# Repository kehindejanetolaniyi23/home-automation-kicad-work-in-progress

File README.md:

# Home Automation Relay and Power Monitoring PCB — Work in Progress

This repository contains my ongoing KiCad PCB design for a home automation relay and power monitoring board.

The project is designed as a multi-channel control and monitoring board for home automation applications. It combines relay switching, power monitoring, sensing interfaces, optocoupler isolation, and onboard power regulation into one PCB design.

This project is still in progress, and I am continuing to improve the routing, board outline, component spacing, and design rule compliance.

## Project Overview

The goal of this project is to design a PCB that can support home automation control and electrical monitoring functions. The board includes relay outputs for switching external loads, sensing sections for voltage/current monitoring, and interface connections for a controller module.

The design is being developed in KiCad and currently includes both schematic and PCB layout files.

## Main Features

* Multi-channel relay switching section
* Optocoupler isolation stage
* Voltage sensing section
* Current sensing transformer section
* Onboard power regulation section
* Screw terminal input/output connectors
* Status indicator LEDs
* Controller/header interface
* Two-layer PCB layout
* KiCad schematic and PCB layout files

## Tools Used

* KiCad
* KiCad Schematic Editor
* KiCad PCB Editor
* KiCad Design Rules Checker

## Repository Files

This repository includes:

* `homeautomation2.kicad_pro` — KiCad project file
* `homeautomation2.kicad_sch` — schematic design file
* `homeautomation2.kicad_pcb` — PCB layout file
* Screenshot images showing the schematic, PCB layout, and current DRC result

## Current Status

Status: **Work in Progress**

The schematic and PCB layout have been created and opened successfully in KiCad. The design already contains the major functional blocks for relay control, sensing, power regulation, and external wiring connections.

The PCB layout is still being improved. Current work includes:

* Completing remaining unrouted connections
* Fixing board outline issues
* Improving component spacing
* Cleaning up silkscreen placement
* Resolving DRC errors and warnings
* Preparing the board for a cleaner final layout
* Generating Gerber files only after the design passes final checks

## Design Notes

The board is intended to combine control and monitoring functions in a compact home automation PCB. The relay section is used for switching loads, while the sensing section supports electrical monitoring. Optocouplers are included to improve isolation between the control and switching sections.

The current PCB layout is functional as a design draft, but it is not yet marked as manufacturing-ready. I am still refining the routing and resolving design rule issues before producing final Gerber fabrication files.

## Next Improvements

The next development steps are:

1. Complete all remaining PCB routing.
2. Fix the Edge.Cuts board outline.
3. Resolve all Design Rule Check errors.
4. Improve relay, terminal block, and sensing section spacing.
5. Clean up text labels and silkscreen placement.
6. Re-run schematic-to-PCB checks.
7. Re-run DRC until the project has zero errors.
8. Export Gerber and drill files after the design is fully cleaned.

## Project Purpose

This project demonstrates my ongoing KiCad PCB design workflow, including schematic capture, PCB layout development, routing, DRC checking, and iterative board improvement.

The design is still under development and will be updated as improvements are made.

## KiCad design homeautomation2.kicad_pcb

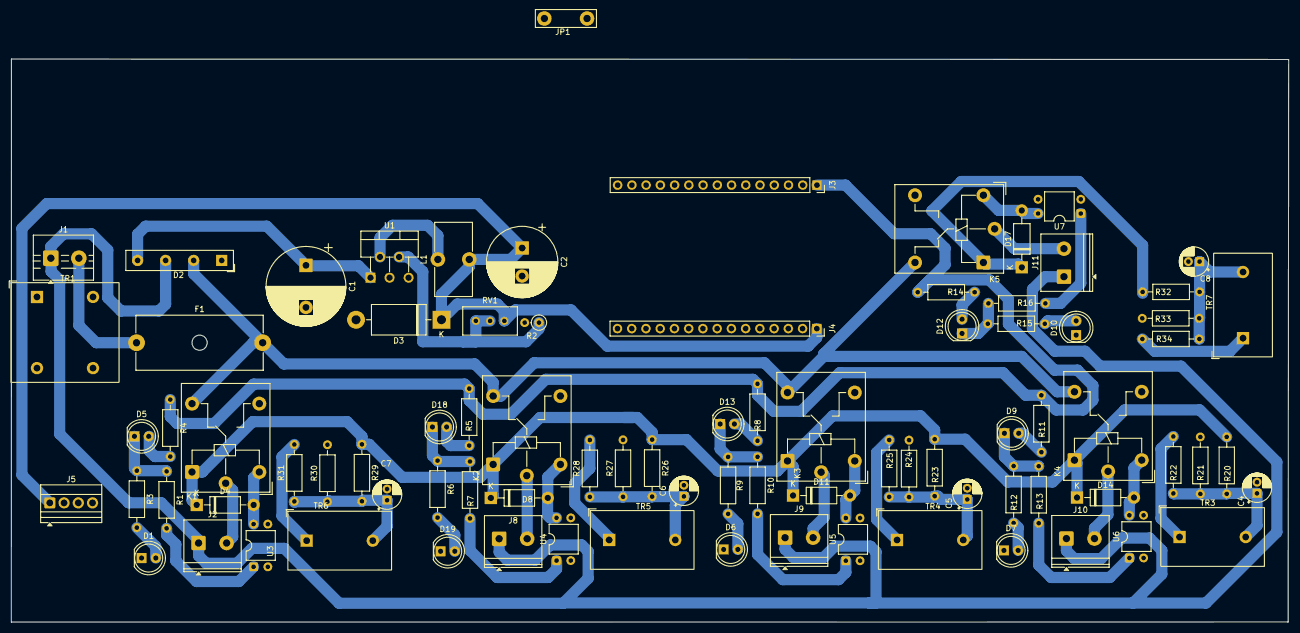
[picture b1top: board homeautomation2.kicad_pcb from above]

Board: 2 copper layers, 227.9 x 100.4 mm, 85 parts (0 on the bottom side), 50 nets.

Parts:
C1: C_Polarized; CP_Radial_D14.0mm_P7.50mm
C2: C_Polarized; CP_Radial_D12.5mm_P5.00mm
C4, C5, C6, C7, C8: C_Small_US; CP_Radial_D5.0mm_P2.00mm
D1, D6, D7, D10, D19: LED; LED_D5.0mm
D2: B500C2300-1500A; Diode_Bridge_19.0x3.5x10.0mm_P5.0mm
D3: 1N5822; D_DO-201AD_P15.24mm_Horizontal
D4, D8, D11, D14, D17: 1N4007; D_DO-41_SOD81_P10.16mm_Horizontal
D5, D9, D12, D13, D18: LED; LED_D5.0mm_Clear
F1: Fuse; Fuseholder_Cylinder-5x20mm_Schurter_0031_8201_Horizontal_Op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
J1: Screw_Terminal_01x02; TerminalBlock_MaiXu_MX126-5.0-02P_1x02_P5.00mm
J2, J8, J9, J10, J11: Screw_Terminal_01x02; TerminalBlock_Phoenix_PT-1,5-2-5.0-H_1x02_P5.00mm_Horizontal
J3, J4: Conn_01x15_Socket; PinSocket_1x15_P2.54mm_Vertical
J5: Conn_01x04_Socket; TerminalBlock_Xinya_XY308-2.54-4P_1x04_P2.54mm_Horizontal
JP1: Jumper_2_Bridged; TestPoint_Bridge_Pitch7.62mm_Drill1.3mm
K1, K2, K3, K4, K5: JQC-3FF-005-1Z; Relay_SPDT_Hongfa_JQC-3FF_0XX-1Z
L1: L_Ferrite_Small; L_Toroid_Vertical_L13.0mm_W6.5mm_P5.60mm
R1, R3, R4, R5, R6, R7, R8, R9, R10, R11, R12, R13, R14, R15, R16, R20, R21, R22, R23, R24, R25, R26, R27, R28, R29, R30, R31, R32, R33, R34: R_Small; R_Axial_DIN0207_L6.3mm_D2.5mm_P10.16mm_Horizontal
R2: R_Small; R_Axial_DIN0207_L6.3mm_D2.5mm_P2.54mm_Vertical
RV1: R_Potentiometer_Small; Potentiometer_Bourns_3296W_Vertical
TR1: ZMPT101K; Transformer_Zeming_ZMPT101K
TR3, TR4, TR5, TR6, TR7: ZMCT103C; Transformer_Zeming_ZMCT103C
U1: LM2596T-5; TO-220-5_P3.4x3.7mm_StaggerOdd_Lead3.8mm_Vertical
U3, U4, U5, U6, U7: PC817; DIP-4_W7.62mm

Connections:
+3.3V: J3.1, R4.1, R5.1, R8.1, R11.1, R14.1
+5V: C2.1, D3.1 (K), D4.1 (K), D8.1 (K), D11.1 (K), D14.1 (K), D17.1 (K), J4.1, J5.1, K1.A1, K2.A1, K3.A1, K4.A1, K5.A1, L1.2, R20.1, R23.1, R26.1, R29.1, R32.1, RV1.1
Earth: C1.2, C2.2, C4.2, C5.2, C6.2, C7.2, C8.2, D1.1 (K), D2.1 (-), D3.2 (A), D6.1 (K), D7.1 (K), D10.1 (K), D19.1 (K), J3.2, J4.2, J5.3, J5.4, R2.2, R21.2, R24.2, R27.2, R30.2, R33.2, U1.3 (GND), U1.5 (~ON/OFF), U3.2, U3.3, U4.2, U4.3, U5.2, U5.3, U6.2, U6.3, U7.2, U7.3
unnamed: C4.1, R20.2, R21.1, R22.1, TR3.2
unnamed: C5.1, R23.2, R24.1, R25.1, TR4.2
unnamed: C6.1, R26.2, R27.1, R28.1, TR5.2
unnamed: C7.1, R29.2, R30.1, R31.1, TR6.2
unnamed: C8.1, R32.2, R33.1, R34.1, TR7.2
unnamed: D1.2 (A), R3.2
unnamed: C1.1, D2.4 (+), U1.1 (VIN)
unnamed: D4.2 (A), K1.A2, U3.4
unnamed: D5.2 (A), R4.2
unnamed: D6.2 (A), R9.2
unnamed: D7.2 (A), R12.2
unnamed: D8.2 (A), K2.A2, U4.4
unnamed: D9.2 (A), R11.2
unnamed: D10.2 (A), R15.2
unnamed: D11.2 (A), K3.A2, U5.4
unnamed: D12.2 (A), R14.2
unnamed: D13.2 (A), R8.2
unnamed: D14.2 (A), K4.A2, U6.4
unnamed: D17.2 (A), K5.A2, U7.4
unnamed: D18.2 (A), R5.2
unnamed: D19.2 (A), R6.2
unnamed: F1.1, J1.2
unnamed: J2.2, K1.11
unnamed: J8.2, K2.11
unnamed: J9.2, K3.11
unnamed: J10.2, K4.11
unnamed: J11.2, K5.11
unnamed: R1.2, U3.1
unnamed: R7.2, U4.1
unnamed: R10.2, U5.1
unnamed: R13.2, U6.1
unnamed: R16.2, U7.1
unnamed: R2.1, RV1.2, RV1.3, U1.4 (FB)
unnamed: L1.1, U1.2 (OUT)
Vout: J4.9, J5.2
cur1: J4.10, R34.2, TR7.1
cur2: J4.11, R22.2, TR3.1
cur3: J4.12, R25.2, TR4.1
cur4: J4.13, R28.2, TR5.1
cur5: J4.14, R31.2, TR6.1
live: D2.2, F1.2, K1.12, K2.12, K3.12, K4.12, K5.12
neutral: D2.3, J1.1, J2.1, J8.1, J9.1, J10.1, J11.1
relay1: D12.1 (K), J4.3, R15.1, R16.1
relay2: D9.1 (K), J4.5, R12.1, R13.1
relay3: D13.1 (K), J4.6, R9.1, R10.1
relay4: D18.1 (K), J4.7, R6.1, R7.1
relay5: D5.1 (K), J4.8, R1.1, R3.1

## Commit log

2026-06-25 Add home automation KiCad work-in-progress files
2026-06-25 Revise README for home automation PCB project
    Expanded project details and features for the home automation PCB design, including current status and next steps.
